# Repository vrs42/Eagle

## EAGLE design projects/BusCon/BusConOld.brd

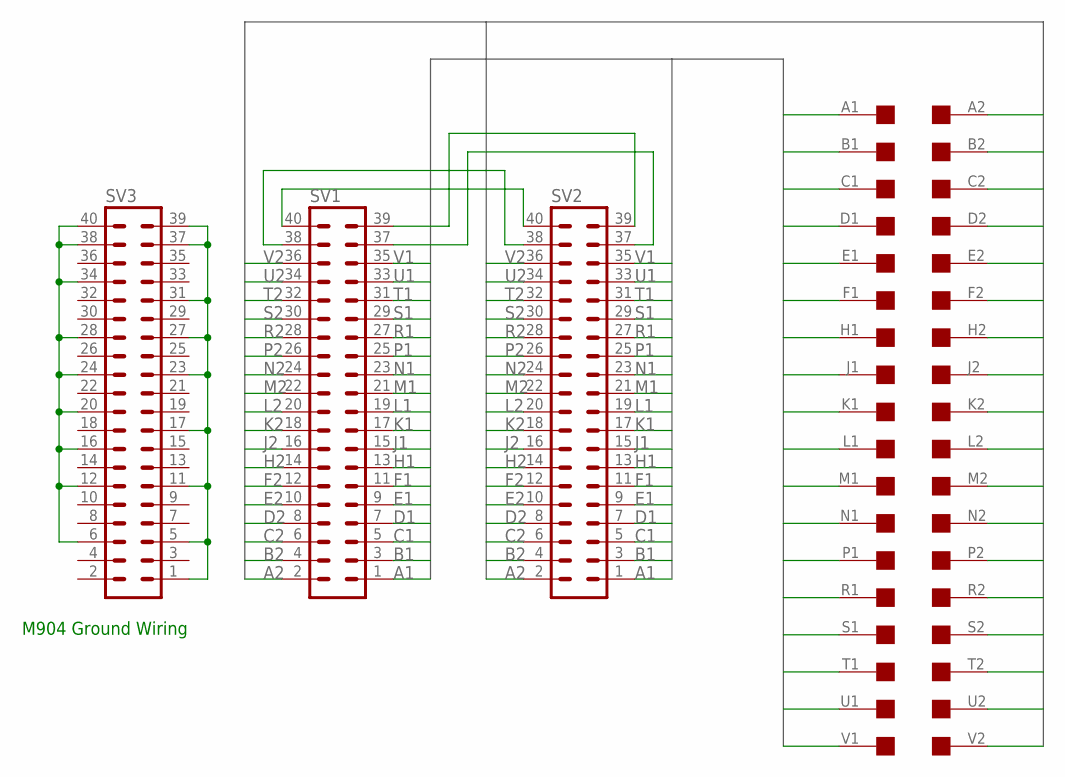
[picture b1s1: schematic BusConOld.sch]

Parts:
SV1, SV2, SV3: MA20-2W
U$1: DEC-FLIPCHIP

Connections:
A1: SV1.1, SV2.1, U$1.A1
A2: SV1.2, SV2.2, U$1.A2
B1: SV1.3, SV2.3, U$1.B1
B2: SV1.4, SV2.4, U$1.B2
C1: SV1.5, SV2.5, U$1.C1
C2: SV1.6, SV2.6, U$1.C2
D1: SV1.7, SV2.7, U$1.D1
D2: SV1.8, SV2.8, U$1.D2
E1: SV1.9, SV2.9, U$1.E1
E2: SV1.10, SV2.10, U$1.E2
F1: SV1.11, SV2.11, U$1.F1
F2: SV1.12, SV2.12, U$1.F2
H1: SV1.13, SV2.13, U$1.H1
H2: SV1.14, SV2.14, U$1.H2
J1: SV1.15, SV2.15, U$1.J1
J2: SV1.16, SV2.16, U$1.J2
K1: SV1.17, SV2.17, U$1.K1
K2: SV1.18, SV2.18, U$1.K2
L1: SV1.19, SV2.19, U$1.L1
L2: SV1.20, SV2.20, U$1.L2
M1: SV1.21, SV2.21, U$1.M1
M2: SV1.22, SV2.22, U$1.M2
N1: SV1.23, SV2.23, U$1.N1
N2: SV1.24, SV2.24, U$1.N2
unnamed: SV1.40, SV2.40
unnamed: SV1.38, SV2.38
unnamed: SV1.37, SV2.37
unnamed: SV1.39, SV2.39
unnamed: SV3.1, SV3.5, SV3.11, SV3.17, SV3.23, SV3.27, SV3.31, SV3.37, SV3.39
unnamed: SV3.6, SV3.12, SV3.16, SV3.20, SV3.24, SV3.28, SV3.34, SV3.38, SV3.40
P1: SV1.25, SV2.25, U$1.P1
P2: SV1.26, SV2.26, U$1.P2
R1: SV1.27, SV2.27, U$1.R1
R2: SV1.28, SV2.28, U$1.R2
S1: SV1.29, SV2.29, U$1.S1
S2: SV1.30, SV2.30, U$1.S2
T1: SV1.31, SV2.31, U$1.T1
T2: SV1.32, SV2.32, U$1.T2
U1: SV1.33, SV2.33, U$1.U1
U2: SV1.34, SV2.34, U$1.U2
V1: SV1.35, SV2.35, U$1.V1
V2: SV1.36, SV2.36, U$1.V2

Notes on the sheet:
M904 Ground Wiring

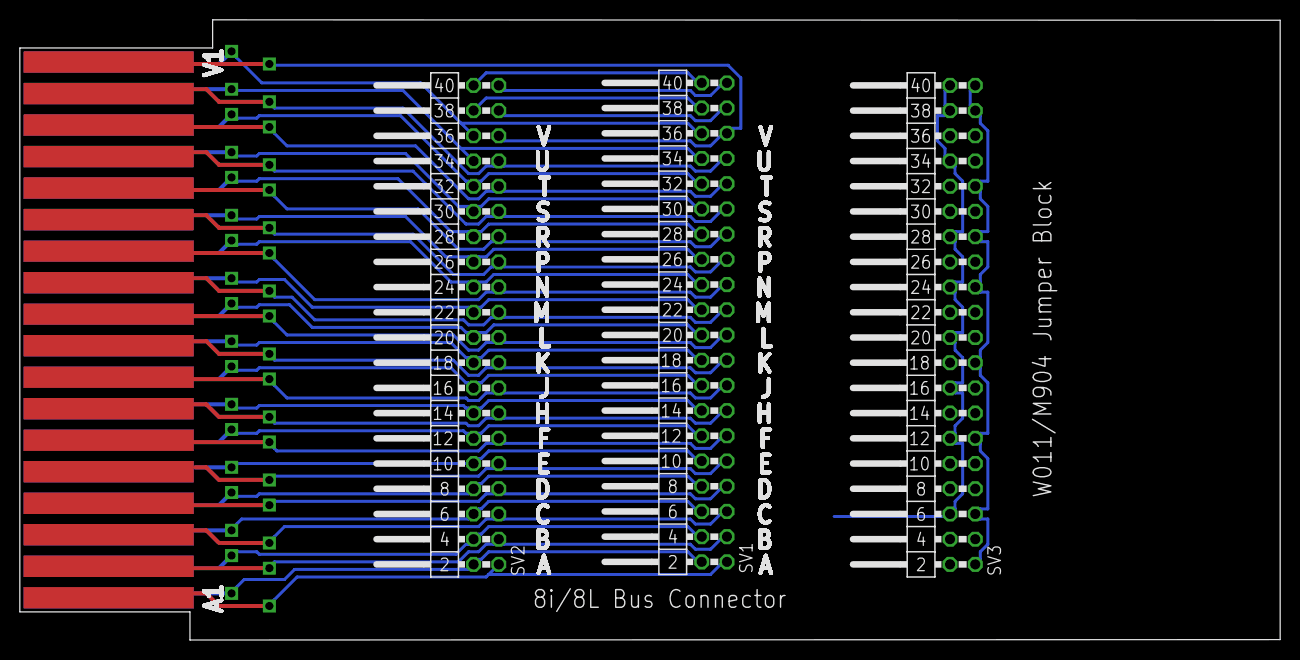
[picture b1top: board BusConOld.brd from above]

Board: 2 copper layers, 127.0 x 62.5 mm, 4 parts (0 on the bottom side), 42 nets.

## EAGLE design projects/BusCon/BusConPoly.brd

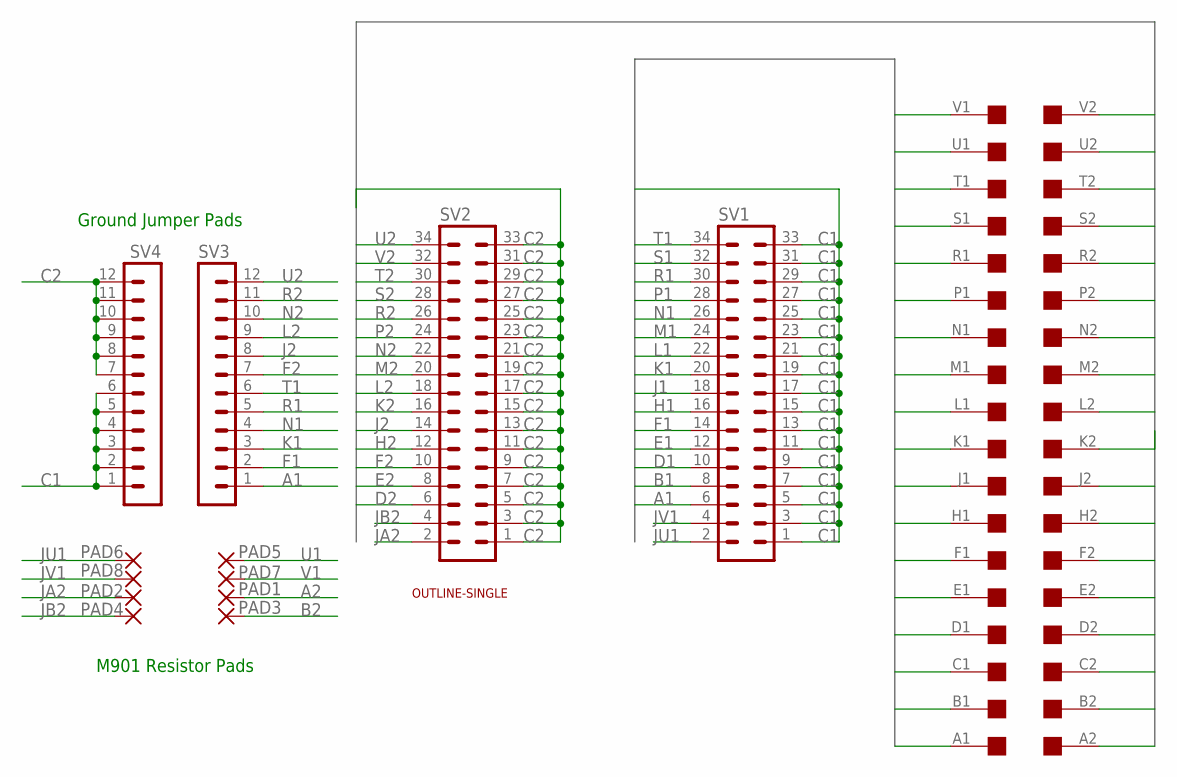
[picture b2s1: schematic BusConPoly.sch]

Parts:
PAD1, PAD2, PAD3, PAD4, PAD5, PAD6, PAD7, PAD8: 1,6/0,8
SV1, SV2: MA17-2
SV3, SV4: MA12-1
U$1: OUTLINE-SINGLE; SINGLE
U$4: EDGE-2CONNECTOR; EDGE-CON2

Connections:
A1: SV1.6, SV3.1, U$4.A1
A2: PAD1.1, U$4.A2
B1: SV1.8, U$4.B1
B2: PAD3.1, U$4.B2
C1: SV1.1, SV1.3, SV1.5, SV1.7, SV1.9, SV1.11, SV1.13, SV1.15, SV1.17, SV1.19, SV1.21, SV1.23, SV1.25, SV1.27, SV1.29, SV1.31, SV1.33, SV4.1, SV4.2, SV4.3, SV4.4, SV4.5, SV4.6, U$4.C1
C2: SV2.1, SV2.3, SV2.5, SV2.7, SV2.9, SV2.11, SV2.13, SV2.15, SV2.17, SV2.19, SV2.21, SV2.23, SV2.25, SV2.27, SV2.29, SV2.31, SV2.33, SV4.7, SV4.8, SV4.9, SV4.10, SV4.11, SV4.12, U$4.C2
D1: SV1.10, U$4.D1
D2: SV2.6, U$4.D2
E1: SV1.12, U$4.E1
E2: SV2.8, U$4.E2
F1: SV1.14, SV3.2, U$4.F1
F2: SV2.10, SV3.7, U$4.F2
H1: SV1.16, U$4.H1
H2: SV2.12, U$4.H2
J1: SV1.18, U$4.J1
J2: SV2.14, SV3.8, U$4.J2
JA2: PAD2.1, SV2.2
JB2: PAD4.1, SV2.4
JU1: PAD6.1, SV1.2
JV1: PAD8.1, SV1.4
K1: SV1.20, SV3.3, U$4.K1
K2: SV2.16, U$4.K2
L1: SV1.22, U$4.L1
L2: SV2.18, SV3.9, U$4.L2
M1: SV1.24, U$4.M1
M2: SV2.20, U$4.M2
N1: SV1.26, SV3.4, U$4.N1
N2: SV2.22, SV3.10, U$4.N2
P1: SV1.28, U$4.P1
P2: SV2.24, U$4.P2
R1: SV1.30, SV3.5, U$4.R1
R2: SV2.26, SV3.11, U$4.R2
S1: SV1.32, U$4.S1
S2: SV2.28, U$4.S2
T1: SV1.34, SV3.6, U$4.T1
T2: SV2.30, U$4.T2
U1: PAD5.1, U$4.U1
U2: SV2.34, SV3.12, U$4.U2
V1: PAD7.1, U$4.V1
V2: SV2.32, U$4.V2

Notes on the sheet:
M901 Resistor Pads
Ground Jumper Pads

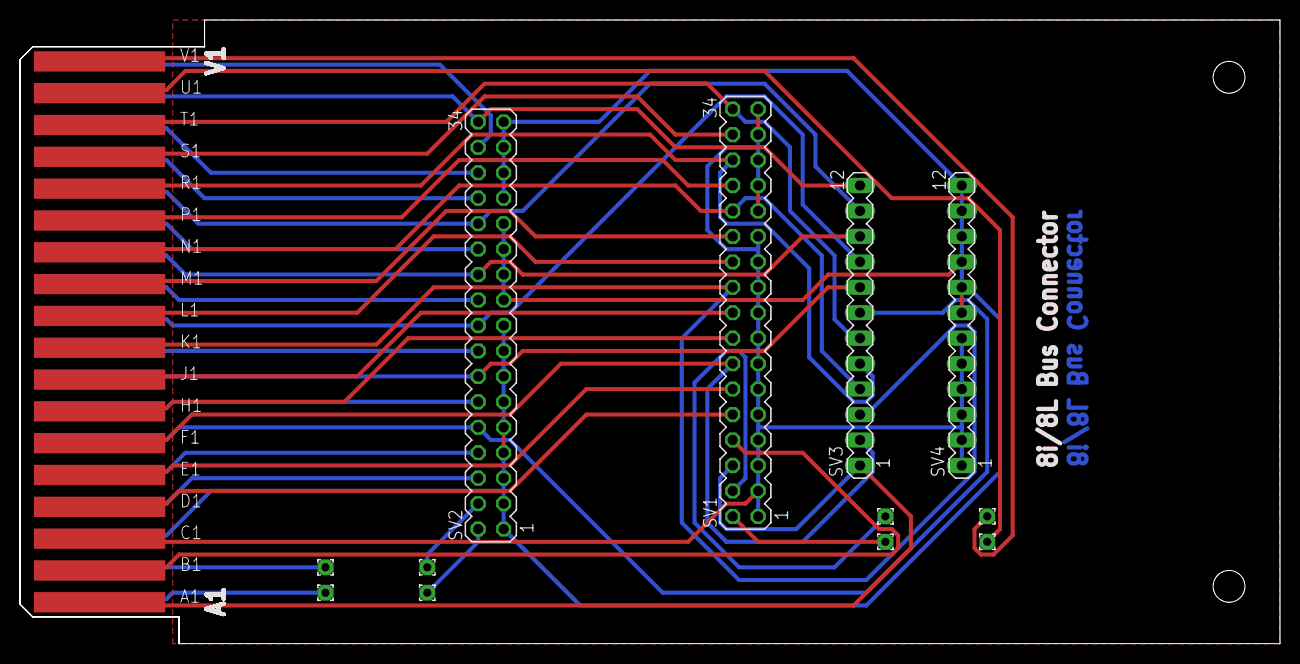
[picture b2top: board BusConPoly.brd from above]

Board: 2 copper layers, 125.7 x 62.2 mm, 14 parts (0 on the bottom side), 40 nets.

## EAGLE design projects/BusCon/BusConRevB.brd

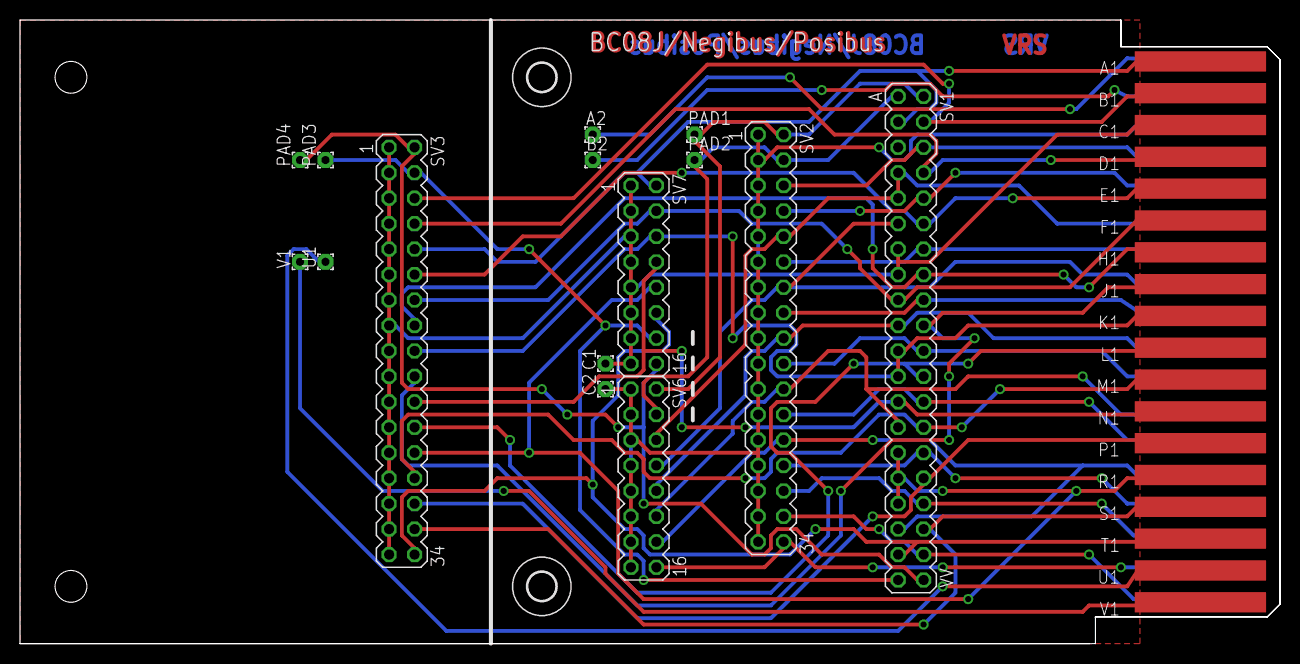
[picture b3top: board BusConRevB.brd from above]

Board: 2 copper layers, 125.7 x 62.2 mm, 19 parts (0 on the bottom side), 40 nets.

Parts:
A2: 1,6/0,8
B2: 1,6/0,8
C1, C2: 1,6/0,8
PAD1, PAD2, PAD3, PAD4: 1,6/0,8
SV1: DEC40PINV
SV2, SV3: MA17-2
SV6, SV7: MA08-2
U1: 1,6/0,8
U$1: OUTLINE-SINGLE-R; SINGLE-R
U$2: EDGE-CON2
U$3, U$4: 2,8
V1: 1,6/0,8

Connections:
-15V: B2.1, U$2.B2
A1: SV1.C, SV3.10, SV7.2, U$2.A1
B1: SV1.D, SV3.6, U$2.B1
C1: C1.1, SV1.P, SV1.S, SV3.1, SV3.3, SV3.5, SV3.7, SV3.9, SV3.11, SV3.13, SV3.15, SV3.17, SV3.19, SV3.21, SV3.23, SV3.25, SV3.27, SV3.29, SV3.31, SV3.33, SV7.1, SV7.3, SV7.5, SV7.7, SV7.9, SV7.11, SV7.13, SV7.15, U$2.C1
C2: C2.1, SV1.E, SV2.1, SV2.3, SV2.5, SV2.7, SV2.9, SV2.11, SV2.13, SV2.15, SV2.17, SV2.19, SV2.21, SV2.23, SV2.25, SV2.27, SV2.29, SV2.31, SV2.33, SV6.1, SV6.3, SV6.5, SV6.7, SV6.9, SV6.11, SV6.13, SV6.15, U$2.C2
D1: SV1.J, SV3.8, U$2.D1
D2: SV1.F, SV2.6, U$2.D2
E1: SV1.N, SV3.12, U$2.E1
E2: SV1.L, SV2.8, U$2.E2
F1: SV1.U, SV3.14, SV7.4, U$2.F1
F2: SV1.H, SV1.K, SV2.10, SV6.6, U$2.F2
H1: SV1.T, SV3.16, U$2.H1
H2: SV1.R, SV2.12, U$2.H2
J1: SV1.X, SV3.20, U$2.J1
J2: SV1.M, SV2.14, SV6.8, U$2.J2
JA2: PAD1.1, SV1.B, SV2.2, SV6.2
JB2: PAD2.1, SV1.A, SV2.4, SV6.4
JU1: PAD3.1, SV1.UU, SV3.4, SV7.14
JV1: PAD4.1, SV1.VV, SV3.2, SV7.16
K1: SV1.AA, SV1.Y, SV3.18, SV7.6, U$2.K1
K2: SV1.V, SV2.16, U$2.K2
L1: SV1.BB, SV3.24, U$2.L1
L2: SV1.W, SV2.18, SV6.10, U$2.L2
M1: SV1.FF, SV3.28, U$2.M1
M2: SV1.Z, SV2.20, U$2.M2
N1: SV1.CC, SV3.22, SV7.8, U$2.N1
N2: SV1.EE, SV2.22, SV6.12, U$2.N2
P1: SV1.LL, SV3.30, U$2.P1
P2: SV1.DD, SV2.24, U$2.P2
R1: SV1.HH, SV1.KK, SV1.MM, SV3.26, SV7.10, U$2.R1
R2: SV1.PP, SV2.26, SV6.14, U$2.R2
S1: SV1.RR, SV3.32, U$2.S1
S2: SV1.JJ, SV2.28, U$2.S2
T1: SV1.SS, SV3.34, SV7.12, U$2.T1
T2: SV1.NN, SV2.30, U$2.T2
U1: U1.1, U$2.U1
U2: SV2.34, SV6.16, U$2.U2
V1: U$2.V1, V1.1
V2: SV1.TT, SV2.32, U$2.V2
VCC: A2.1, U$2.A2

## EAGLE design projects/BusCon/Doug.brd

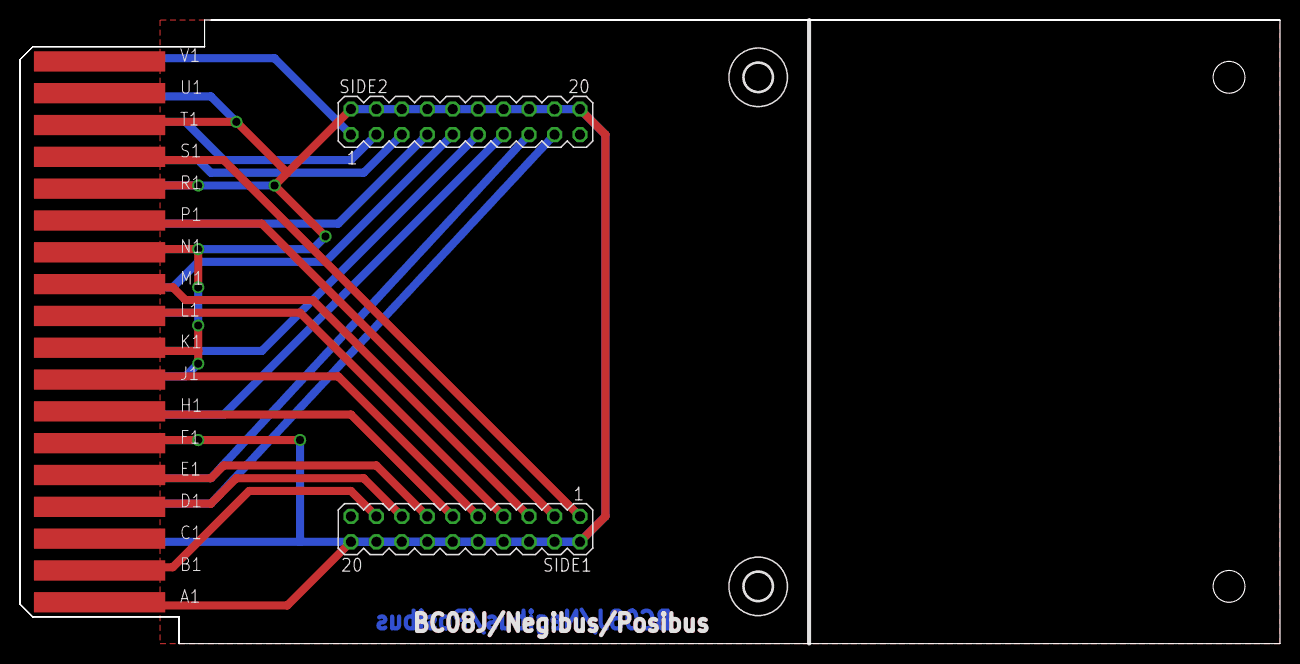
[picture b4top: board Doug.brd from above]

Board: 2 copper layers, 125.7 x 62.2 mm, 6 parts (0 on the bottom side), 19 nets.

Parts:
SIDE1, SIDE2: 10x2; MA10-2
U$1: OUTLINE-SINGLE-R; SINGLE-R
U$2: EDGE; EDGE-CON2
U$3, U$4: 2,8

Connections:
B1: SIDE1.17, U$2.B1
D1: SIDE1.15, U$2.D1
D2: SIDE2.17, U$2.D2
E1: SIDE1.13, U$2.E1
E2: SIDE2.15, U$2.E2
GND: SIDE1.2, SIDE1.4, SIDE1.6, SIDE1.8, SIDE1.10, SIDE1.12, SIDE1.14, SIDE1.16, SIDE1.18, SIDE1.20, SIDE2.2, SIDE2.4, SIDE2.6, SIDE2.8, SIDE2.10, SIDE2.12, SIDE2.14, SIDE2.16, SIDE2.18, SIDE2.20, U$2.A1, U$2.C2, U$2.F1, U$2.F2, U$2.J2, U$2.K1, U$2.L2, U$2.N1, U$2.N2, U$2.R1, U$2.R2, U$2.T1, U$2.U2
H1: SIDE1.11, U$2.H1
H2: SIDE2.13, U$2.H2
J1: SIDE1.9, U$2.J1
K2: SIDE2.11, U$2.K2
L1: SIDE1.7, U$2.L1
M1: SIDE1.5, U$2.M1
M2: SIDE2.9, U$2.M2
P1: SIDE1.3, U$2.P1
P2: SIDE2.7, U$2.P2
S1: SIDE1.1, U$2.S1
S2: SIDE2.5, U$2.S2
T2: SIDE2.3, U$2.T2
V2: SIDE2.1, U$2.V2

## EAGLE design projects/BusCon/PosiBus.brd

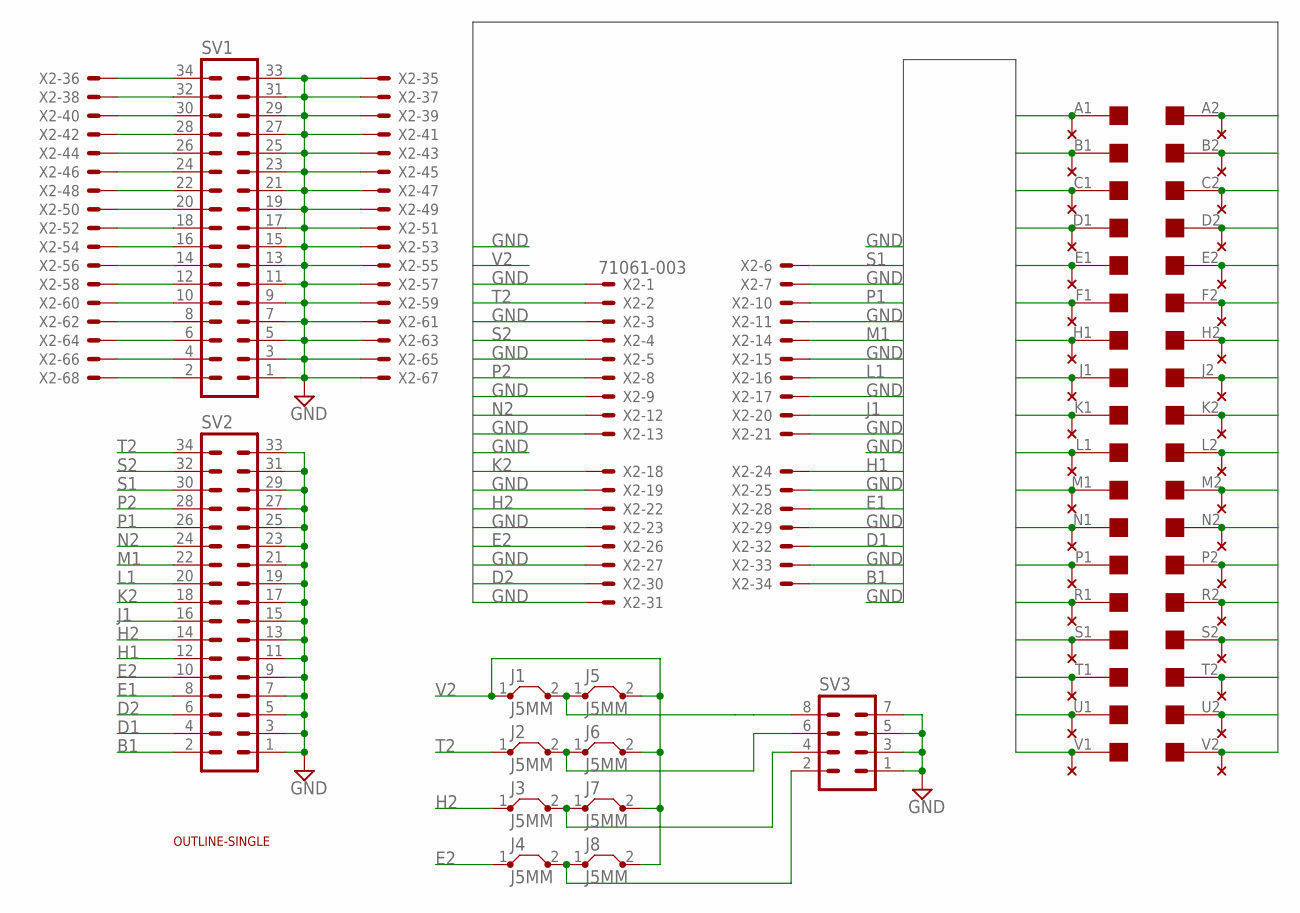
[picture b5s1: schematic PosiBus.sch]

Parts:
EDGE1: EDGE-2CONNECTOR; EDGE-CON2
J1, J2, J3, J4, J5, J6, J7, J8: J5MM; 05
SV1, SV2: ML34
SV3: MA04-2
U$2: OUTLINE-SINGLE; SINGLE
U$3: THRU-HOLE2; THRU-HOLEB
X2: 71061-003; 71061-0003

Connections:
A2: EDGE1.A2, U$3.A2
B1: EDGE1.B1, SV2.2, U$3.B1, X2.34
B2: EDGE1.B2, U$3.B2
D1: EDGE1.D1, SV2.4, U$3.D1, X2.32
D2: EDGE1.D2, SV2.6, U$3.D2, X2.30
E1: EDGE1.E1, SV2.8, U$3.E1, X2.28
E2: EDGE1.E2, J4.1, SV2.10, U$3.E2, X2.26
GND: EDGE1.A1, EDGE1.C1, EDGE1.C2, EDGE1.F1, EDGE1.F2, EDGE1.J2, EDGE1.K1, EDGE1.L2, EDGE1.M2, EDGE1.N1, EDGE1.R1, EDGE1.R2, EDGE1.T1, EDGE1.U2, SV1.1, SV1.3, SV1.5, SV1.7, SV1.9, SV1.11, SV1.13, SV1.15, SV1.17, SV1.19, SV1.21, SV1.23, SV1.25, SV1.27, SV1.29, SV1.31, SV1.33, SV2.1, SV2.3, SV2.5, SV2.7, SV2.9, SV2.11, SV2.13, SV2.15, SV2.17, SV2.19, SV2.21, SV2.23, SV2.25, SV2.27, SV2.29, SV2.31, SV2.33, SV3.1, SV3.3, SV3.5, SV3.7, U$3.A1, U$3.C1, U$3.C2, U$3.F1, U$3.F2, U$3.J2, U$3.K1, U$3.L2, U$3.M2, U$3.N1, U$3.R1, U$3.R2, U$3.T1, U$3.U2, X2.1, X2.3, X2.5, X2.7, X2.9, X2.11, X2.13, X2.15, X2.17, X2.19, X2.21, X2.23, X2.25, X2.27, X2.29, X2.31, X2.33, X2.35, X2.37, X2.39, X2.41, X2.43, X2.45, X2.47, X2.49, X2.51, X2.53, X2.55, X2.57, X2.59, X2.61, X2.63, X2.65, X2.67
H1: EDGE1.H1, SV2.12, U$3.H1, X2.24
H2: EDGE1.H2, J3.1, SV2.14, U$3.H2, X2.22
J1: EDGE1.J1, SV2.16, U$3.J1, X2.20
K2: EDGE1.K2, SV2.18, U$3.K2, X2.18
L1: EDGE1.L1, SV2.20, U$3.L1, X2.16
M1: EDGE1.M1, SV2.22, U$3.M1, X2.14
N2: EDGE1.N2, SV2.24, U$3.N2, X2.12
unnamed: SV1.34, X2.36
unnamed: SV1.4, X2.66
unnamed: SV1.32, X2.38
unnamed: SV1.30, X2.40
unnamed: SV1.28, X2.42
unnamed: SV1.26, X2.44
unnamed: SV1.2, X2.68
unnamed: J1.2, J5.1, SV3.8
unnamed: J2.2, J6.1, SV3.6
unnamed: J3.2, J7.1, SV3.4
unnamed: SV1.24, X2.46
unnamed: J4.2, J8.1, SV3.2
unnamed: SV1.22, X2.48
unnamed: SV1.20, X2.50
unnamed: SV1.18, X2.52
unnamed: SV1.16, X2.54
unnamed: SV1.14, X2.56
unnamed: SV1.12, X2.58
unnamed: SV1.10, X2.60
unnamed: SV1.8, X2.62
unnamed: SV1.6, X2.64
P1: EDGE1.P1, SV2.26, U$3.P1, X2.10
P2: EDGE1.P2, SV2.28, U$3.P2, X2.8
S1: EDGE1.S1, SV2.30, U$3.S1, X2.6
S2: EDGE1.S2, SV2.32, U$3.S2, X2.4
T2: EDGE1.T2, J2.1, SV2.34, U$3.T2, X2.2
U1: EDGE1.U1, U$3.U1
V1: EDGE1.V1, U$3.V1
V2: EDGE1.V2, J1.1, J5.2, J6.2, J7.2, J8.2, U$3.V2

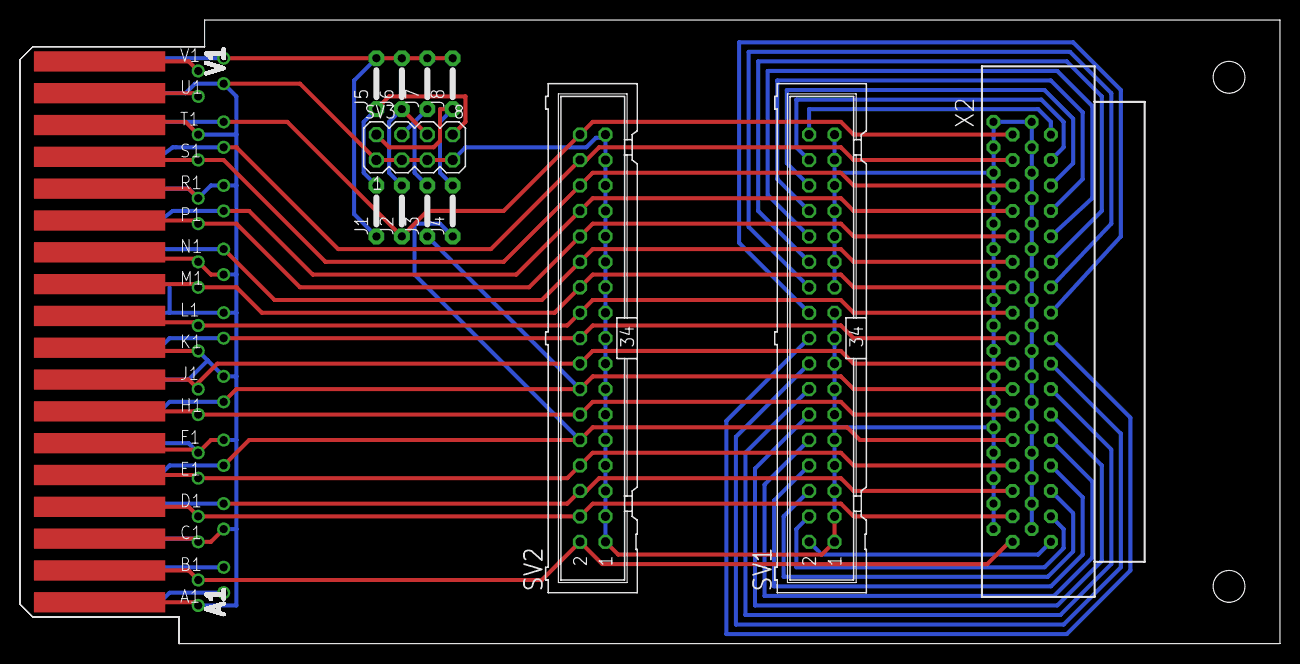
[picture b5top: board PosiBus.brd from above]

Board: 2 copper layers, 125.7 x 62.2 mm, 15 parts (0 on the bottom side), 44 nets.

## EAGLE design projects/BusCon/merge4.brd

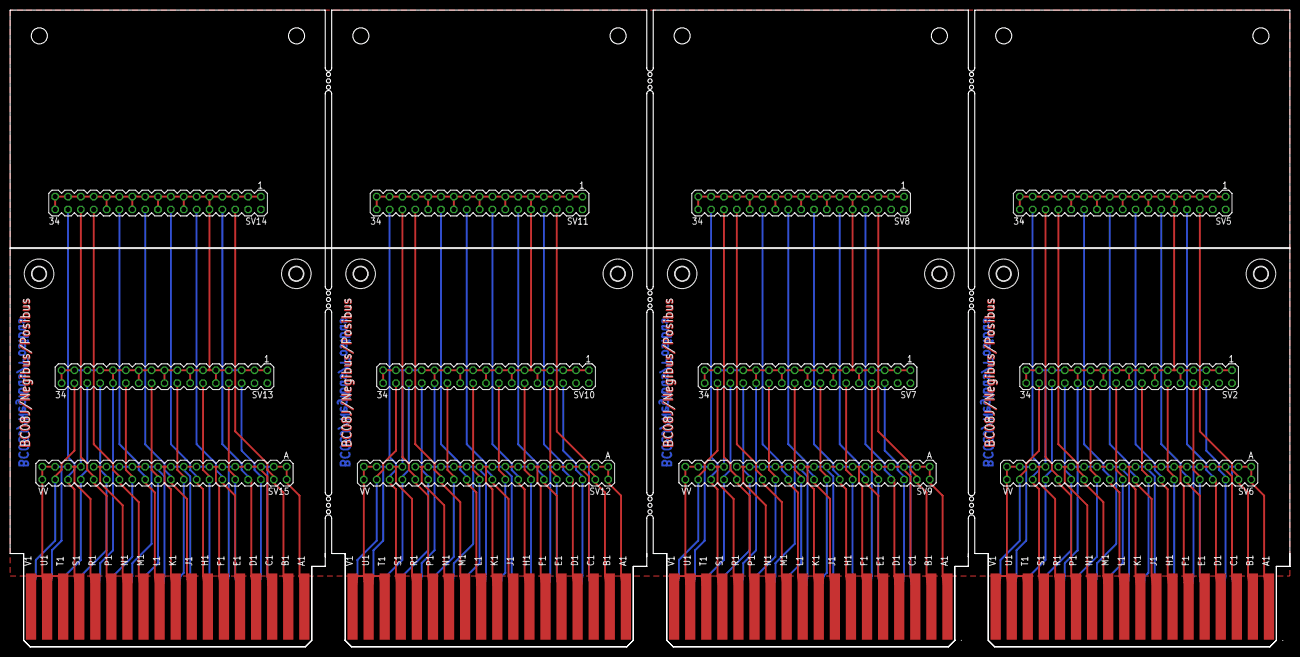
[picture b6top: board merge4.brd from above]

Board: 2 copper layers, 252.7 x 125.7 mm, 25 parts (0 on the bottom side), 73 nets.

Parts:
SV2, SV5, SV7, SV8, SV10, SV11, SV13, SV14: MA17-2
SV6, SV9, SV12, SV15: DEC40PIN
U$5: DECPROTO; DECPROTO1111
U$6, U$10, U$14, U$18: EDGE-CON2
U$8, U$9, U$12, U$13, U$16, U$17, U$20, U$21: 2,8

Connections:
B2: SV5.6, SV6.D, U$6.B1
B3: SV8.6, SV9.D, U$10.B1
B4: SV11.6, SV12.D, U$14.B1
B5: SV14.6, SV15.D, U$18.B1
D3: SV2.6, SV6.F, U$6.D2
D4: SV5.8, SV6.J, U$6.D1
D5: SV7.6, SV9.F, U$10.D2
D6: SV8.8, SV9.J, U$10.D1
D7: SV10.6, SV12.F, U$14.D2
D8: SV11.8, SV12.J, U$14.D1
D9: SV13.6, SV15.F, U$18.D2
D10: SV14.8, SV15.J, U$18.D1
E3: SV2.8, SV6.L, U$6.E2
E4: SV5.12, SV6.N, U$6.E1
E5: SV7.8, SV9.L, U$10.E2
E6: SV8.12, SV9.N, U$10.E1
E7: SV10.8, SV12.L, U$14.E2
E8: SV11.12, SV12.N, U$14.E1
E9: SV13.8, SV15.L, U$18.E2
E10: SV14.12, SV15.N, U$18.E1
GND: SV2.1, SV2.3, SV2.5, SV2.7, SV2.9, SV2.10, SV2.11, SV2.13, SV2.14, SV2.15, SV2.17, SV2.18, SV2.19, SV2.21, SV2.22, SV2.23, SV2.25, SV2.26, SV2.27, SV2.29, SV2.31, SV2.33, SV2.34, SV5.1, SV5.3, SV5.5, SV5.7, SV5.9, SV5.10, SV5.11, SV5.13, SV5.14, SV5.15, SV5.17, SV5.18, SV5.19, SV5.21, SV5.22, SV5.23, SV5.25, SV5.26, SV5.27, SV5.29, SV5.31, SV5.33, SV5.34, SV6.A, SV6.AA, SV6.B, SV6.C, SV6.CC, SV6.E, SV6.EE, SV6.H, SV6.HH, SV6.K, SV6.KK, SV6.M, SV6.MM, SV6.P, SV6.PP, SV6.S, SV6.SS, SV6.U, SV6.UU, SV6.VV, SV6.W, SV6.Y, SV7.1, SV7.3, SV7.5, SV7.7, SV7.9, SV7.10, SV7.11, SV7.13, SV7.14, SV7.15, SV7.17, SV7.18, SV7.19, SV7.21, SV7.22, SV7.23, SV7.25, SV7.26, SV7.27, SV7.29, SV7.31, SV7.33, SV7.34, SV8.1, SV8.3, SV8.5, SV8.7, SV8.9, SV8.10, SV8.11, SV8.13, SV8.14, SV8.15, SV8.17, SV8.18, SV8.19, SV8.21, SV8.22, SV8.23, SV8.25, SV8.26, SV8.27, SV8.29, SV8.31, SV8.33, SV8.34, SV9.A, SV9.AA, SV9.B, SV9.C, SV9.CC, SV9.E, SV9.EE, SV9.H, SV9.HH, SV9.K, SV9.KK, SV9.M, SV9.MM, SV9.P, SV9.PP, SV9.S, SV9.SS, SV9.U, SV9.UU, SV9.VV, SV9.W, SV9.Y, SV10.1, SV10.3, SV10.5, SV10.7, SV10.9, SV10.10, SV10.11, SV10.13, SV10.14, SV10.15, SV10.17, SV10.18, SV10.19, SV10.21, SV10.22, SV10.23, SV10.25, SV10.26, SV10.27, SV10.29, SV10.31, SV10.33, SV10.34, SV11.1, SV11.3, SV11.5, SV11.7, SV11.9, SV11.10, SV11.11, SV11.13, SV11.14, SV11.15, SV11.17, SV11.18, SV11.19, SV11.21, SV11.22, SV11.23, SV11.25, SV11.26, SV11.27, SV11.29, SV11.31, SV11.33, SV11.34, SV12.A, SV12.AA, SV12.B, SV12.C, SV12.CC, SV12.E, SV12.EE, SV12.H, SV12.HH, SV12.K, SV12.KK, SV12.M, SV12.MM, SV12.P, SV12.PP, SV12.S, SV12.SS, SV12.U, SV12.UU, SV12.VV, SV12.W, SV12.Y, SV13.1, SV13.3, SV13.5, SV13.7, SV13.9, SV13.10, SV13.11, SV13.13, SV13.14, SV13.15, SV13.17, SV13.18, SV13.19, SV13.21, SV13.22, SV13.23, SV13.25, SV13.26, SV13.27, SV13.29, SV13.31, SV13.33, SV13.34, SV14.1, SV14.3, SV14.5, SV14.7, SV14.9, SV14.10, SV14.11, SV14.13, SV14.14, SV14.15, SV14.17, SV14.18, SV14.19, SV14.21, SV14.22, SV14.23, SV14.25, SV14.26, SV14.27, SV14.29, SV14.31, SV14.33, SV14.34, SV15.A, SV15.AA, SV15.B, SV15.C, SV15.CC, SV15.E, SV15.EE, SV15.H, SV15.HH, SV15.K, SV15.KK, SV15.M, SV15.MM, SV15.P, SV15.PP, SV15.S, SV15.SS, SV15.U, SV15.UU, SV15.VV, SV15.W, SV15.Y, U$6.A1, U$6.C1, U$6.C2, U$6.F1, U$6.F2, U$6.J2, U$6.K1, U$6.L2, U$6.N1, U$6.N2, U$6.R1, U$6.R2, U$6.T1, U$6.U1, U$6.U2, U$6.V1, U$10.A1, U$10.C1, U$10.C2, U$10.F1, U$10.F2, U$10.J2, U$10.K1, U$10.L2, U$10.N1, U$10.N2, U$10.R1, U$10.R2, U$10.T1, U$10.U1, U$10.U2, U$10.V1, U$14.A1, U$14.C1, U$14.C2, U$14.F1, U$14.F2, U$14.J2, U$14.K1, U$14.L2, U$14.N1, U$14.N2, U$14.R1, U$14.R2, U$14.T1, U$14.U1, U$14.U2, U$14.V1, U$18.A1, U$18.C1, U$18.C2, U$18.F1, U$18.F2, U$18.J2, U$18.K1, U$18.L2, U$18.N1, U$18.N2, U$18.R1, U$18.R2, U$18.T1, U$18.U1, U$18.U2, U$18.V1
H3: SV2.12, SV6.R, U$6.H2
H4: SV5.16, SV6.T, U$6.H1
H5: SV7.12, SV9.R, U$10.H2
H6: SV8.16, SV9.T, U$10.H1
H7: SV10.12, SV12.R, U$14.H2
H8: SV11.16, SV12.T, U$14.H1
H9: SV13.12, SV15.R, U$18.H2
H10: SV14.16, SV15.T, U$18.H1
J2: SV5.20, SV6.X, U$6.J1
J3: SV8.20, SV9.X, U$10.J1
J4: SV11.20, SV12.X, U$14.J1
J5: SV14.20, SV15.X, U$18.J1
K1: SV2.16, SV6.V, U$6.K2
K3: SV7.16, SV9.V, U$10.K2
K4: SV10.16, SV12.V, U$14.K2
K5: SV13.16, SV15.V, U$18.K2
L2: SV5.24, SV6.BB, U$6.L1
L3: SV8.24, SV9.BB, U$10.L1
L4: SV11.24, SV12.BB, U$14.L1
L5: SV14.24, SV15.BB, U$18.L1
M3: SV2.20, SV6.Z, U$6.M2
M4: SV5.28, SV6.FF, U$6.M1
M5: SV7.20, SV9.Z, U$10.M2
M6: SV8.28, SV9.FF, U$10.M1
M7: SV10.20, SV12.Z, U$14.M2
M8: SV11.28, SV12.FF, U$14.M1
M9: SV13.20, SV15.Z, U$18.M2
M10: SV14.28, SV15.FF, U$18.M1
P3: SV2.24, SV6.DD, U$6.P2
P4: SV5.30, SV6.LL, U$6.P1
P5: SV7.24, SV9.DD, U$10.P2
P6: SV8.30, SV9.LL, U$10.P1
P7: SV10.24, SV12.DD, U$14.P2
P8: SV11.30, SV12.LL, U$14.P1
P9: SV13.24, SV15.DD, U$18.P2
P10: SV14.30, SV15.LL, U$18.P1
S3: SV2.28, SV6.JJ, U$6.S2
S4: SV5.32, SV6.RR, U$6.S1
S5: SV7.28, SV9.JJ, U$10.S2
S6: SV8.32, SV9.RR, U$10.S1
S7: SV10.28, SV12.JJ, U$14.S2
S8: SV11.32, SV12.RR, U$14.S1
S9: SV13.28, SV15.JJ, U$18.S2
S10: SV14.32, SV15.RR, U$18.S1
T1: SV2.30, SV6.NN, U$6.T2
T3: SV7.30, SV9.NN, U$10.T2
T4: SV10.30, SV12.NN, U$14.T2
T5: SV13.30, SV15.NN, U$18.T2
V1: SV2.32, SV6.TT, U$6.V2
V3: SV7.32, SV9.TT, U$10.V2
V4: SV10.32, SV12.TT, U$14.V2
V5: SV13.32, SV15.TT, U$18.V2

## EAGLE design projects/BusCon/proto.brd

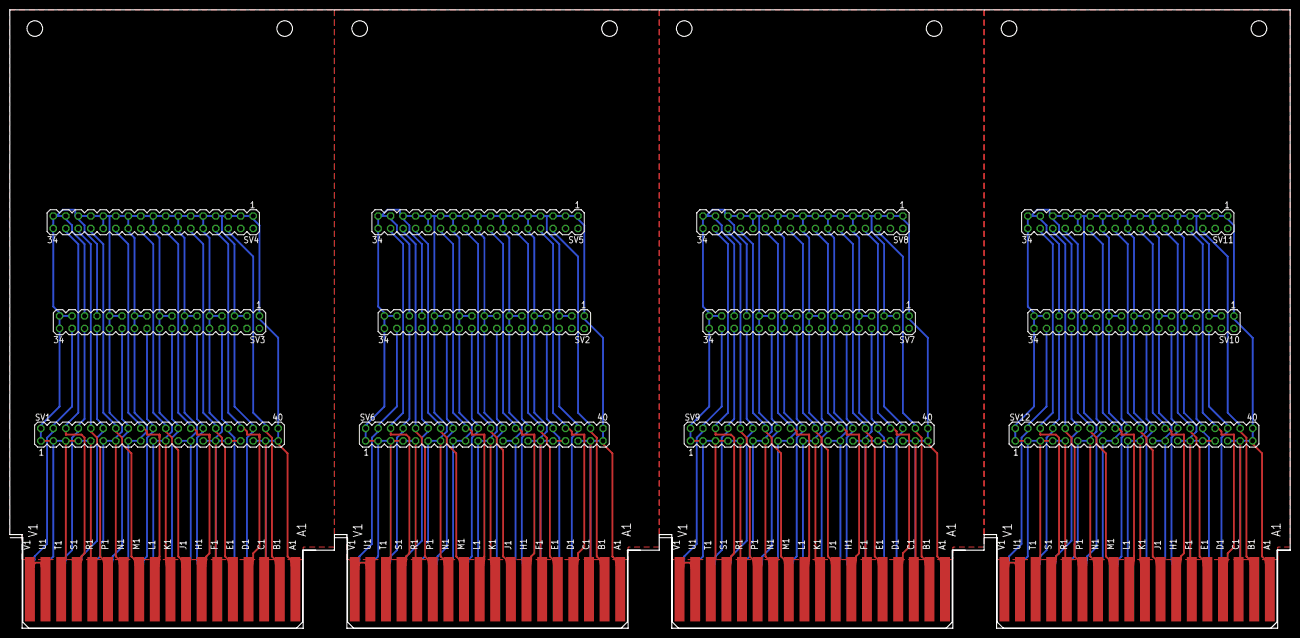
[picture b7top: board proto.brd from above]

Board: 2 copper layers, 260.3 x 125.7 mm, 17 parts (0 on the bottom side), 73 nets.

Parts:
E$1: DECPROTO
SV1, SV6, SV9, SV12: MA20-2
SV2, SV3, SV4, SV5, SV7, SV8, SV10, SV11: MA17-2
U$1, U$2, U$3, U$5: EDGE-CON2

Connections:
B1: SV1.38, SV4.6, U$2.B1
B2: SV5.6, SV6.38, U$3.B1
B3: SV8.6, SV9.38, U$1.B1
B4: SV11.6, SV12.38, U$5.B1
D1: SV1.34, SV4.8, U$2.D1
D2: SV1.36, SV3.6, U$2.D2
D3: SV2.6, SV6.36, U$3.D2
D4: SV5.8, SV6.34, U$3.D1
D5: SV7.6, SV9.36, U$1.D2
D6: SV8.8, SV9.34, U$1.D1
D7: SV10.6, SV12.36, U$5.D2
D8: SV11.8, SV12.34, U$5.D1
E1: SV1.30, SV4.12, U$2.E1
E2: SV1.32, SV3.8, U$2.E2
E3: SV2.8, SV6.32, U$3.E2
E4: SV5.12, SV6.30, U$3.E1
E5: SV7.8, SV9.32, U$1.E2
E6: SV8.12, SV9.30, U$1.E1
E7: SV10.8, SV12.32, U$5.E2
E8: SV11.12, SV12.30, U$5.E1
GND: SV1.1, SV1.2, SV1.3, SV1.5, SV1.7, SV1.9, SV1.11, SV1.13, SV1.15, SV1.17, SV1.19, SV1.21, SV1.23, SV1.25, SV1.27, SV1.29, SV1.31, SV1.33, SV1.35, SV1.37, SV1.39, SV1.40, SV2.1, SV2.3, SV2.5, SV2.7, SV2.9, SV2.10, SV2.11, SV2.13, SV2.14, SV2.15, SV2.17, SV2.18, SV2.19, SV2.21, SV2.22, SV2.23, SV2.25, SV2.26, SV2.27, SV2.29, SV2.31, SV2.33, SV2.34, SV3.1, SV3.3, SV3.5, SV3.7, SV3.9, SV3.10, SV3.11, SV3.13, SV3.14, SV3.15, SV3.17, SV3.18, SV3.19, SV3.21, SV3.22, SV3.23, SV3.25, SV3.26, SV3.27, SV3.29, SV3.31, SV3.33, SV3.34, SV4.1, SV4.3, SV4.5, SV4.7, SV4.9, SV4.10, SV4.11, SV4.13, SV4.14, SV4.15, SV4.17, SV4.18, SV4.19, SV4.21, SV4.22, SV4.23, SV4.25, SV4.26, SV4.27, SV4.29, SV4.31, SV4.33, SV4.34, SV5.1, SV5.3, SV5.5, SV5.7, SV5.9, SV5.10, SV5.11, SV5.13, SV5.14, SV5.15, SV5.17, SV5.18, SV5.19, SV5.21, SV5.22, SV5.23, SV5.25, SV5.26, SV5.27, SV5.29, SV5.31, SV5.33, SV5.34, SV6.1, SV6.2, SV6.3, SV6.5, SV6.7, SV6.9, SV6.11, SV6.13, SV6.15, SV6.17, SV6.19, SV6.21, SV6.23, SV6.25, SV6.27, SV6.29, SV6.31, SV6.33, SV6.35, SV6.37, SV6.39, SV6.40, SV7.1, SV7.3, SV7.5, SV7.7, SV7.9, SV7.10, SV7.11, SV7.13, SV7.14, SV7.15, SV7.17, SV7.18, SV7.19, SV7.21, SV7.22, SV7.23, SV7.25, SV7.26, SV7.27, SV7.29, SV7.31, SV7.33, SV7.34, SV8.1, SV8.3, SV8.5, SV8.7, SV8.9, SV8.10, SV8.11, SV8.13, SV8.14, SV8.15, SV8.17, SV8.18, SV8.19, SV8.21, SV8.22, SV8.23, SV8.25, SV8.26, SV8.27, SV8.29, SV8.31, SV8.33, SV8.34, SV9.1, SV9.2, SV9.3, SV9.5, SV9.7, SV9.9, SV9.11, SV9.13, SV9.15, SV9.17, SV9.19, SV9.21, SV9.23, SV9.25, SV9.27, SV9.29, SV9.31, SV9.33, SV9.35, SV9.37, SV9.39, SV9.40, SV10.1, SV10.3, SV10.5, SV10.7, SV10.9, SV10.10, SV10.11, SV10.13, SV10.14, SV10.15, SV10.17, SV10.18, SV10.19, SV10.21, SV10.22, SV10.23, SV10.25, SV10.26, SV10.27, SV10.29, SV10.31, SV10.33, SV10.34, SV11.1, SV11.3, SV11.5, SV11.7, SV11.9, SV11.10, SV11.11, SV11.13, SV11.14, SV11.15, SV11.17, SV11.18, SV11.19, SV11.21, SV11.22, SV11.23, SV11.25, SV11.26, SV11.27, SV11.29, SV11.31, SV11.33, SV11.34, SV12.1, SV12.2, SV12.3, SV12.5, SV12.7, SV12.9, SV12.11, SV12.13, SV12.15, SV12.17, SV12.19, SV12.21, SV12.23, SV12.25, SV12.27, SV12.29, SV12.31, SV12.33, SV12.35, SV12.37, SV12.39, SV12.40, U$1.A1, U$1.C1, U$1.C2, U$1.F1, U$1.F2, U$1.J2, U$1.K1, U$1.L2, U$1.N1, U$1.N2, U$1.R1, U$1.R2, U$1.T1, U$1.U1, U$1.U2, U$1.V1, U$2.A1, U$2.C1, U$2.C2, U$2.F1, U$2.F2, U$2.J2, U$2.K1, U$2.L2, U$2.N1, U$2.N2, U$2.R1, U$2.R2, U$2.T1, U$2.U1, U$2.U2, U$2.V1, U$3.A1, U$3.C1, U$3.C2, U$3.F1, U$3.F2, U$3.J2, U$3.K1, U$3.L2, U$3.N1, U$3.N2, U$3.R1, U$3.R2, U$3.T1, U$3.U1, U$3.U2, U$3.V1, U$5.A1, U$5.C1, U$5.C2, U$5.F1, U$5.F2, U$5.J2, U$5.K1, U$5.L2, U$5.N1, U$5.N2, U$5.R1, U$5.R2, U$5.T1, U$5.U1, U$5.U2, U$5.V1
H1: SV1.26, SV4.16, U$2.H1
H2: SV1.28, SV3.12, U$2.H2
H3: SV2.12, SV6.28, U$3.H2
H4: SV5.16, SV6.26, U$3.H1
H5: SV7.12, SV9.28, U$1.H2
H6: SV8.16, SV9.26, U$1.H1
H7: SV10.12, SV12.28, U$5.H2
H8: SV11.16, SV12.26, U$5.H1
J1: SV1.22, SV4.20, U$2.J1
J2: SV5.20, SV6.22, U$3.J1
J3: SV8.20, SV9.22, U$1.J1
J4: SV11.20, SV12.22, U$5.J1
K1: SV2.16, SV6.24, U$3.K2
K2: SV1.24, SV3.16, U$2.K2
K3: SV7.16, SV9.24, U$1.K2
K4: SV10.16, SV12.24, U$5.K2
L1: SV1.18, SV4.24, U$2.L1
L2: SV5.24, SV6.18, U$3.L1
L3: SV8.24, SV9.18, U$1.L1
L4: SV11.24, SV12.18, U$5.L1
M1: SV1.14, SV4.28, U$2.M1
M2: SV1.20, SV3.20, U$2.M2
M3: SV2.20, SV6.20, U$3.M2
M4: SV5.28, SV6.14, U$3.M1
M5: SV7.20, SV9.20, U$1.M2
M6: SV8.28, SV9.14, U$1.M1
M7: SV10.20, SV12.20, U$5.M2
M8: SV11.28, SV12.14, U$5.M1
P1: SV1.10, SV4.30, U$2.P1
P2: SV1.16, SV3.24, U$2.P2
P3: SV2.24, SV6.16, U$3.P2
P4: SV5.30, SV6.10, U$3.P1
P5: SV7.24, SV9.16, U$1.P2
P6: SV8.30, SV9.10, U$1.P1
P7: SV10.24, SV12.16, U$5.P2
P8: SV11.30, SV12.10, U$5.P1
S1: SV1.6, SV4.32, U$2.S1
S2: SV1.12, SV3.28, U$2.S2
S3: SV2.28, SV6.12, U$3.S2
S4: SV5.32, SV6.6, U$3.S1
S5: SV7.28, SV9.12, U$1.S2
S6: SV8.32, SV9.6, U$1.S1
S7: SV10.28, SV12.12, U$5.S2
S8: SV11.32, SV12.6, U$5.S1
T1: SV2.30, SV6.8, U$3.T2
T2: SV1.8, SV3.30, U$2.T2
T3: SV7.30, SV9.8, U$1.T2
T4: SV10.30, SV12.8, U$5.T2
V1: SV2.32, SV6.4, U$3.V2
V2: SV1.4, SV3.32, U$2.V2
V3: SV7.32, SV9.4, U$1.V2
V4: SV10.32, SV12.4, U$5.V2
